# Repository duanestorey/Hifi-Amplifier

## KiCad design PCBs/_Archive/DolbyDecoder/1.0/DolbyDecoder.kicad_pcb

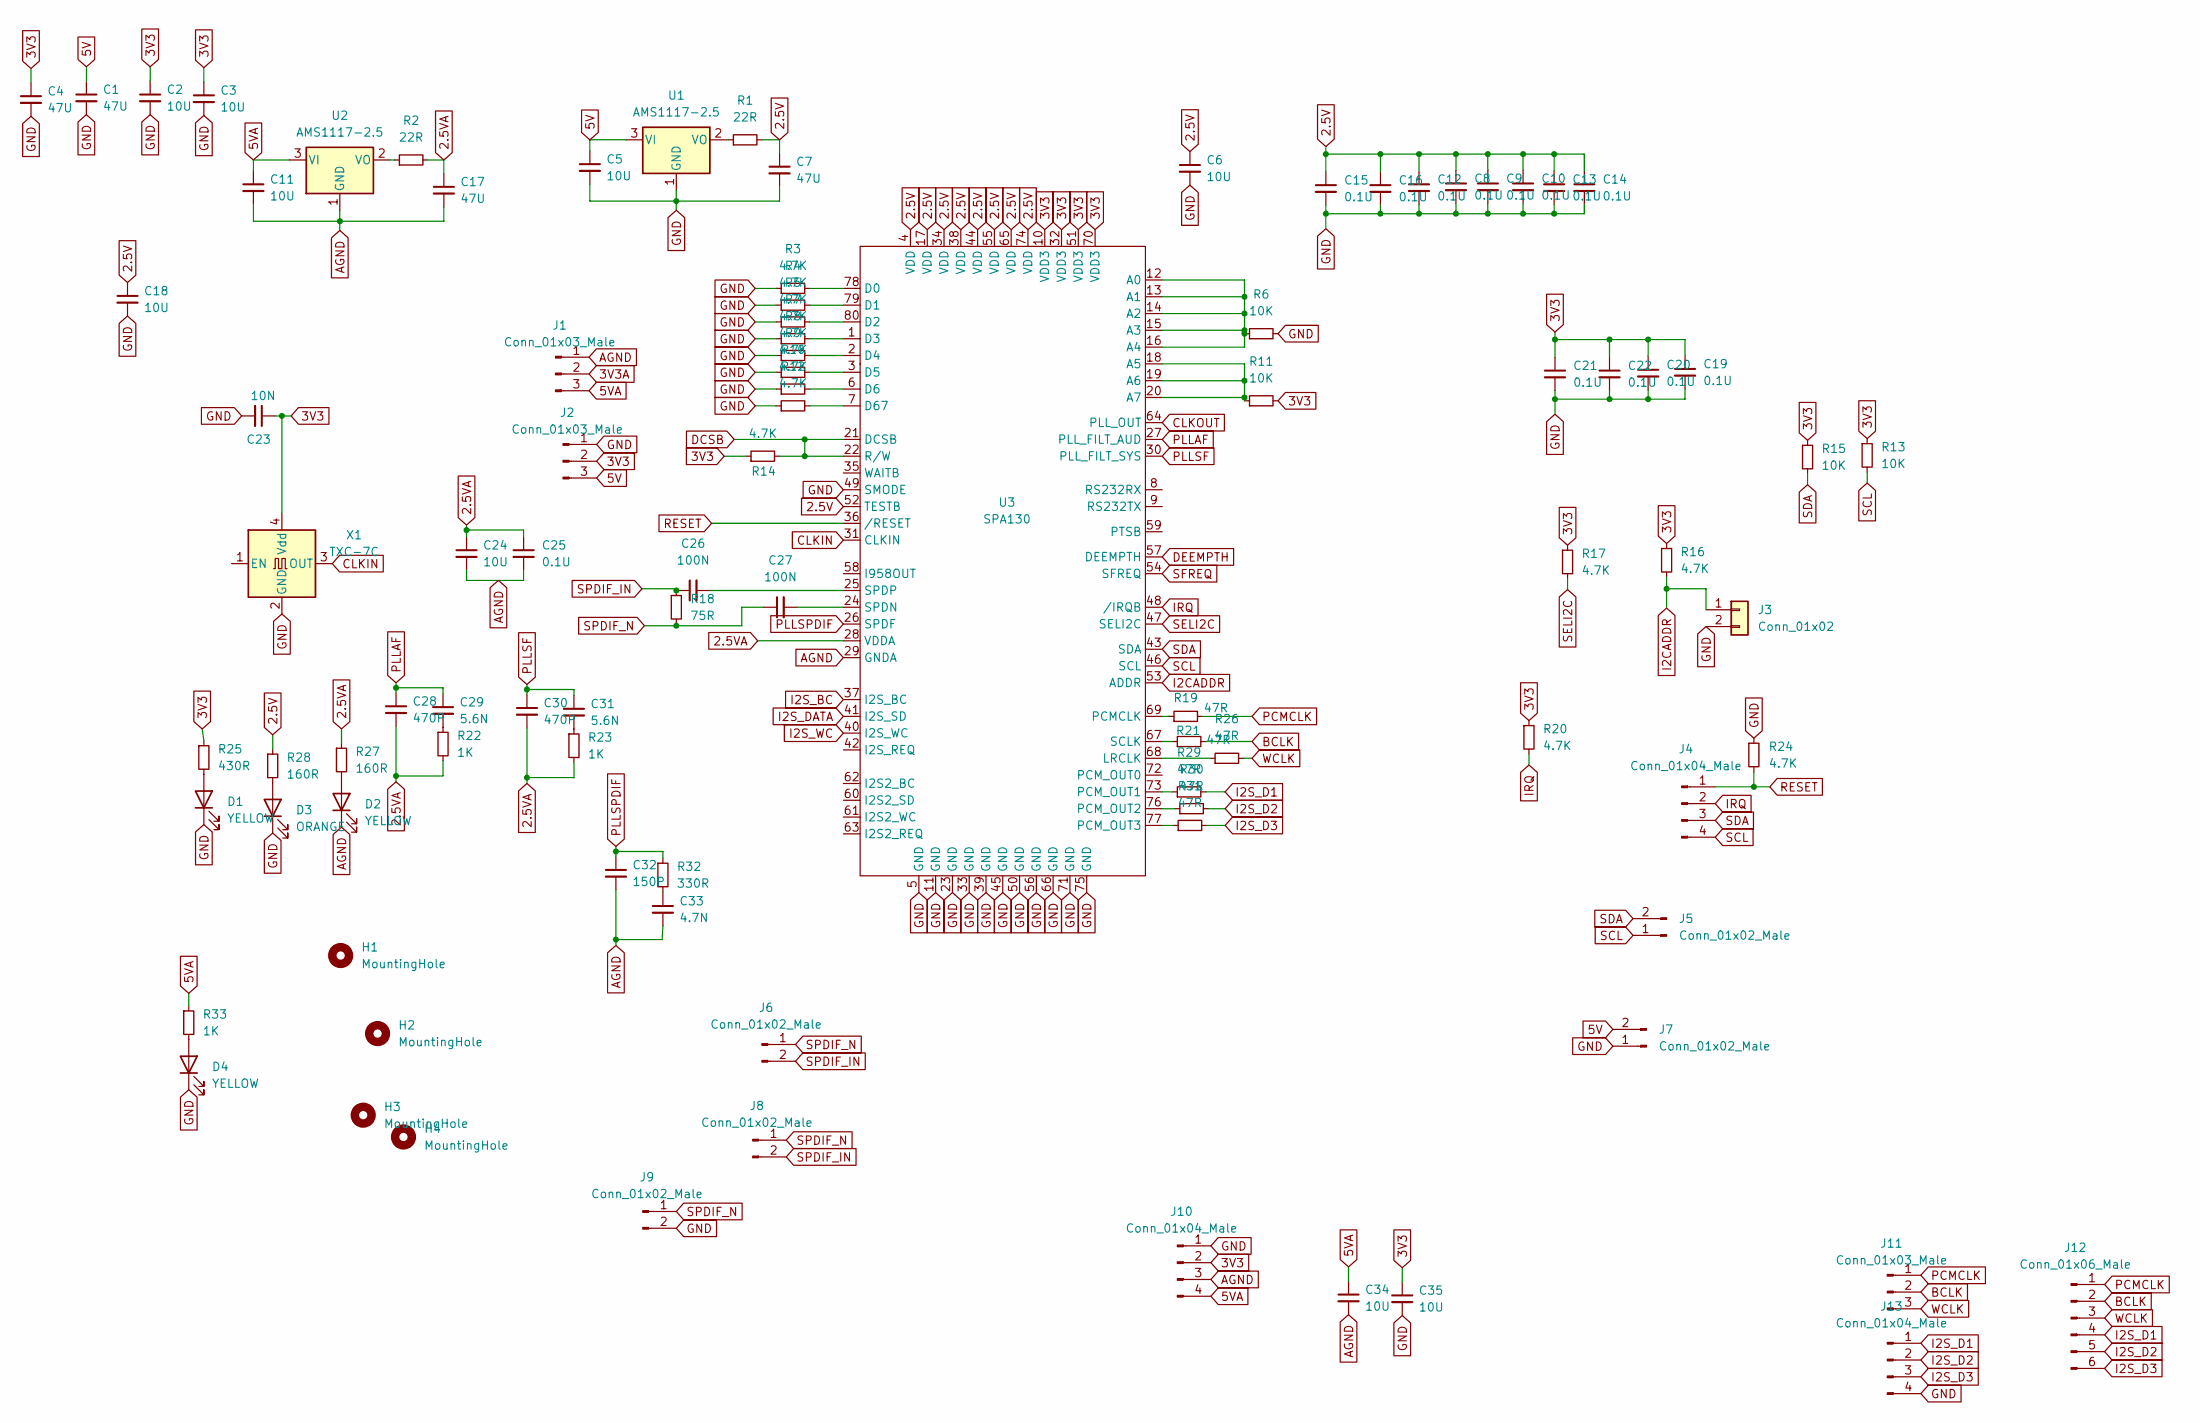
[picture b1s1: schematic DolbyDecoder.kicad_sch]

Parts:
C1, C4, C7, C17: 47U; C_1206_3216Metric_Pad1.33x1.80mm_HandSolder
C2, C3, C6, C18, C34, C35: 10U; C_1206_3216Metric_Pad1.33x1.80mm_HandSolder
C5, C11, C24: 10U; C_0805_2012Metric_Pad1.18x1.45mm_HandSolder
C8, C9, C10, C12, C13, C14, C15, C16, C19, C20, C21, C22, C25: 0.1U; C_0603_1608Metric_Pad1.08x0.95mm_HandSolder
C23: 10N; C_0603_1608Metric_Pad1.08x0.95mm_HandSolder
C26, C27: 100N; C_0805_2012Metric_Pad1.18x1.45mm_HandSolder
C28, C30: 470P; C_0805_2012Metric_Pad1.18x1.45mm_HandSolder
C29, C31: 5.6N; C_0805_2012Metric_Pad1.18x1.45mm_HandSolder
C32: 150P; C_0805_2012Metric_Pad1.18x1.45mm_HandSolder
C33: 4.7N; C_0805_2012Metric_Pad1.18x1.45mm_HandSolder
D1, D2, D4: YELLOW; LED_0805_2012Metric_Pad1.15x1.40mm_HandSolder
D3: ORANGE; LED_0805_2012Metric_Pad1.15x1.40mm_HandSolder
H1, H2, H3, H4: MountingHole; MountingHole_3.2mm_M3
J1, J2, J11: Conn_01x03_Male; JST_PH_B3B-PH-K_1x03_P2.00mm_Vertical
J3: Conn_01x02; PinHeader_1x02_P2.54mm_Vertical
J4, J10, J13: Conn_01x04_Male; JST_PH_B4B-PH-K_1x04_P2.00mm_Vertical
J5, J6, J7: Conn_01x02_Male; JST_PH_B2B-PH-K_1x02_P2.00mm_Vertical
J8, J9: Conn_01x02_Male; PinHeader_1x02_P2.54mm_Vertical
J12: Conn_01x06_Male; PinHeader_1x06_P2.54mm_Vertical
R1, R2: 22R; R_0805_2012Metric_Pad1.20x1.40mm_HandSolder
R3, R4, R5, R7, R8, R9, R10, R12, R14, R16, R17, R20, R24: 4.7K; R_0603_1608Metric_Pad0.98x0.95mm_HandSolder
R6, R11, R13, R15: 10K; R_0603_1608Metric_Pad0.98x0.95mm_HandSolder
R18: 75R; R_0603_1608Metric_Pad0.98x0.95mm_HandSolder
R19, R21, R26, R29, R30, R31: 47R; R_0805_2012Metric_Pad1.20x1.40mm_HandSolder
R22, R23, R33: 1K; R_0603_1608Metric_Pad0.98x0.95mm_HandSolder
R25: 430R; R_0603_1608Metric_Pad0.98x0.95mm_HandSolder
R27, R28: 160R; R_0603_1608Metric_Pad0.98x0.95mm_HandSolder
R32: 330R; R_0603_1608Metric_Pad0.98x0.95mm_HandSolder
U1, U2: AMS1117-2.5; SOT-223
U3: SPA130; LQFP-80_14x14mm_P0.65mm
X1: TXC-7C; Oscillator_SMD_EuroQuartz_XO32-4Pin_3.2x2.5mm_HandSoldering

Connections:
2.5V: C6.1, C7.1, C8.1, C9.1, C10.1, C12.1, C13.1, C14.1, C15.1, C16.1, C18.1, R1.2, R28.1, U3.4 (VDD), U3.17 (VDD), U3.34 (VDD), U3.38 (VDD), U3.44 (VDD), U3.52 (TESTB), U3.55 (VDD), U3.65 (VDD), U3.74 (VDD)
2.5VA: C17.1, C24.1, C25.1, C28.2, C30.2, R2.2, R22.2, R23.2, R27.1, U3.28 (VDDA)
3V3: C2.1, C3.1, C4.1, C19.1, C20.1, C21.1, C22.1, C23.1, C35.1, J2.2, J10.2, R11.2, R13.1, R14.1, R15.1, R16.1, R17.1, R20.1, R25.1, U3.10 (VDD3), U3.32 (VDD3), U3.51 (VDD3), U3.70 (VDD3), X1.4 (Vdd)
3V3A: J1.2
5V: C1.1, C5.1, J2.3, J7.2, U1.3 (VI)
5VA: C11.1, C34.1, J1.3, J10.4, R33.1, U2.3 (VI)
AGND: C11.2, C17.2, C24.2, C25.2, C32.2, C33.2, C34.2, D2.1 (K), J1.1, J10.3, U2.1 (GND), U3.29 (GNDA)
BCLK: J11.2, J12.2, R21.2
CLKIN: U3.31 (CLKIN), X1.3 (OUT)
CLKOUT: U3.64 (PLL_OUT)
DCSB: R14.2, U3.21 (DCSB), U3.22 (R/W)
DEEMPTH: U3.57 (DEEMPTH)
GND: C1.2, C2.2, C3.2, C4.2, C5.2, C6.2, C7.2, C8.2, C9.2, C10.2, C12.2, C13.2, C14.2, C15.2, C16.2, C18.2, C19.2, C20.2, C21.2, C22.2, C23.2, C35.2, D1.1 (K), D3.1 (K), D4.1 (K), J2.1, J3.2, J7.1, J9.2, J10.1, J13.4, R3.1, R4.1, R5.1, R6.2, R7.1, R8.1, R9.1, R10.1, R12.1, R24.1, U1.1 (GND), U3.5 (GND), U3.11 (GND), U3.23 (GND), U3.33 (GND), U3.39 (GND), U3.45 (GND), U3.49 (SMODE), U3.50 (GND), U3.56 (GND), U3.66 (GND), U3.71 (GND), U3.75 (GND), X1.2 (GND)
I2CADDR: J3.1, R16.2, U3.53 (ADDR)
I2S_BC: U3.37 (I2S_BC)
I2S_D1: J12.4, J13.1, R29.2
I2S_D2: J12.5, J13.2, R30.2
I2S_D3: J12.6, J13.3, R31.2
I2S_DATA: U3.41 (I2S_SD)
I2S_WC: U3.40 (I2S_WC)
IRQ: J4.2, R20.2, U3.48 (/IRQB)
unnamed: C29.2, R22.1
unnamed: C31.2, R23.1
unnamed: C33.1, R32.2
unnamed: D1.2 (A), R25.2
unnamed: D2.2 (A), R27.2
unnamed: D3.2 (A), R28.2
unnamed: D4.2 (A), R33.2
unnamed: R1.1, U1.2 (VO)
unnamed: R2.1, U2.2 (VO)
unnamed: R6.1, U3.12 (A0), U3.13 (A1), U3.14 (A2), U3.15 (A3), U3.16 (A4)
unnamed: R11.1, U3.18 (A5), U3.19 (A6), U3.20 (A7)
unnamed: R3.2, U3.78 (D0)
unnamed: R4.2, U3.79 (D1)
unnamed: R5.2, U3.80 (D2)
unnamed: R7.2, U3.1 (D3)
unnamed: R8.2, U3.2 (D4)
unnamed: R9.2, U3.3 (D5)
unnamed: R10.2, U3.6 (D6)
unnamed: R12.2, U3.7 (D67)
unnamed: R26.1, U3.68 (LRCLK)
unnamed: R19.1, U3.69 (PCMCLK)
unnamed: R29.1, U3.73 (PCM_OUT1)
unnamed: R30.1, U3.76 (PCM_OUT2)
unnamed: R31.1, U3.77 (PCM_OUT3)
unnamed: R21.1, U3.67 (SCLK)
unnamed: C27.2, U3.24 (SPDN)
unnamed: C26.2, U3.25 (SPDP)
PCMCLK: J11.1, J12.1, R19.2
PLLAF: C28.1, C29.1, U3.27 (PLL_FILT_AUD)
PLLSF: C30.1, C31.1, U3.30 (PLL_FILT_SYS)
PLLSPDIF: C32.1, R32.1, U3.26 (SPDF)
RESET: J4.1, R24.2, U3.36 (/RESET)
SCL: J4.4, J5.1, R13.2, U3.46 (SCL)
SDA: J4.3, J5.2, R15.2, U3.43 (SDA)
SELI2C: R17.2, U3.47 (SELI2C)
SFREQ: U3.54 (SFREQ)
SPDIF_IN: C26.1, J6.2, J8.2, R18.1
SPDIF_N: C27.1, J6.1, J8.1, J9.1, R18.2
WCLK: J11.3, J12.3, R26.2

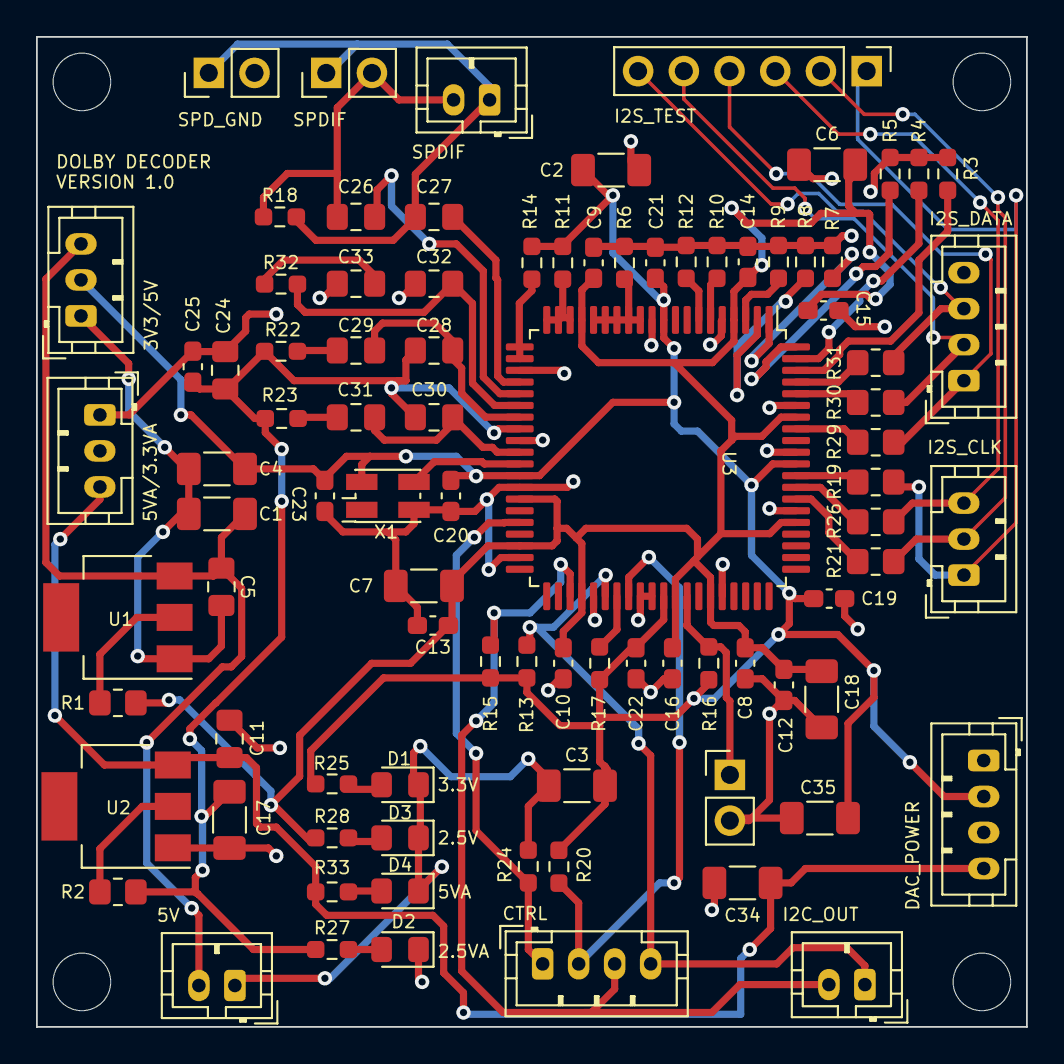
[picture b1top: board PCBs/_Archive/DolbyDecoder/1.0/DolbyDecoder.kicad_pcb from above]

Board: 2 copper layers, 55.0 x 55.0 mm, 93 parts (0 on the bottom side), 53 nets.

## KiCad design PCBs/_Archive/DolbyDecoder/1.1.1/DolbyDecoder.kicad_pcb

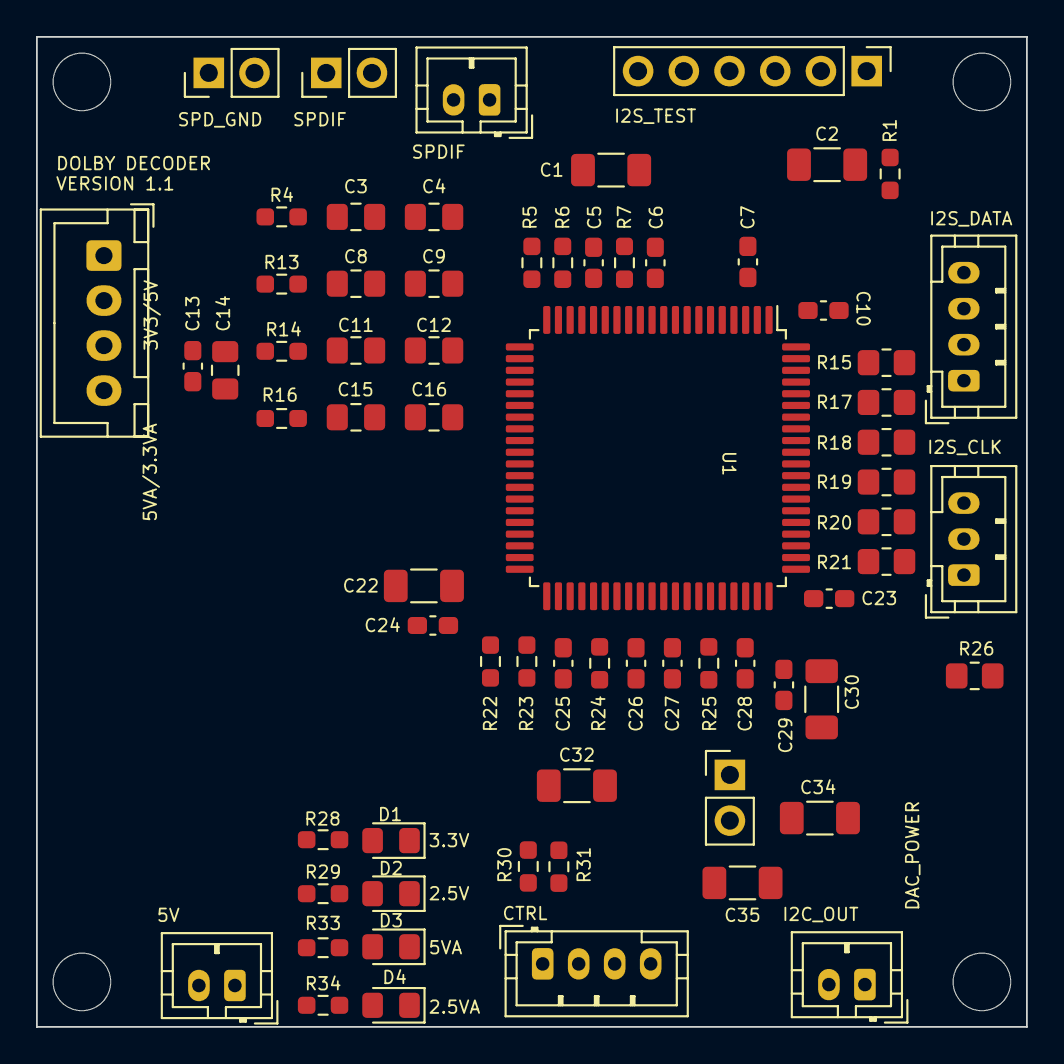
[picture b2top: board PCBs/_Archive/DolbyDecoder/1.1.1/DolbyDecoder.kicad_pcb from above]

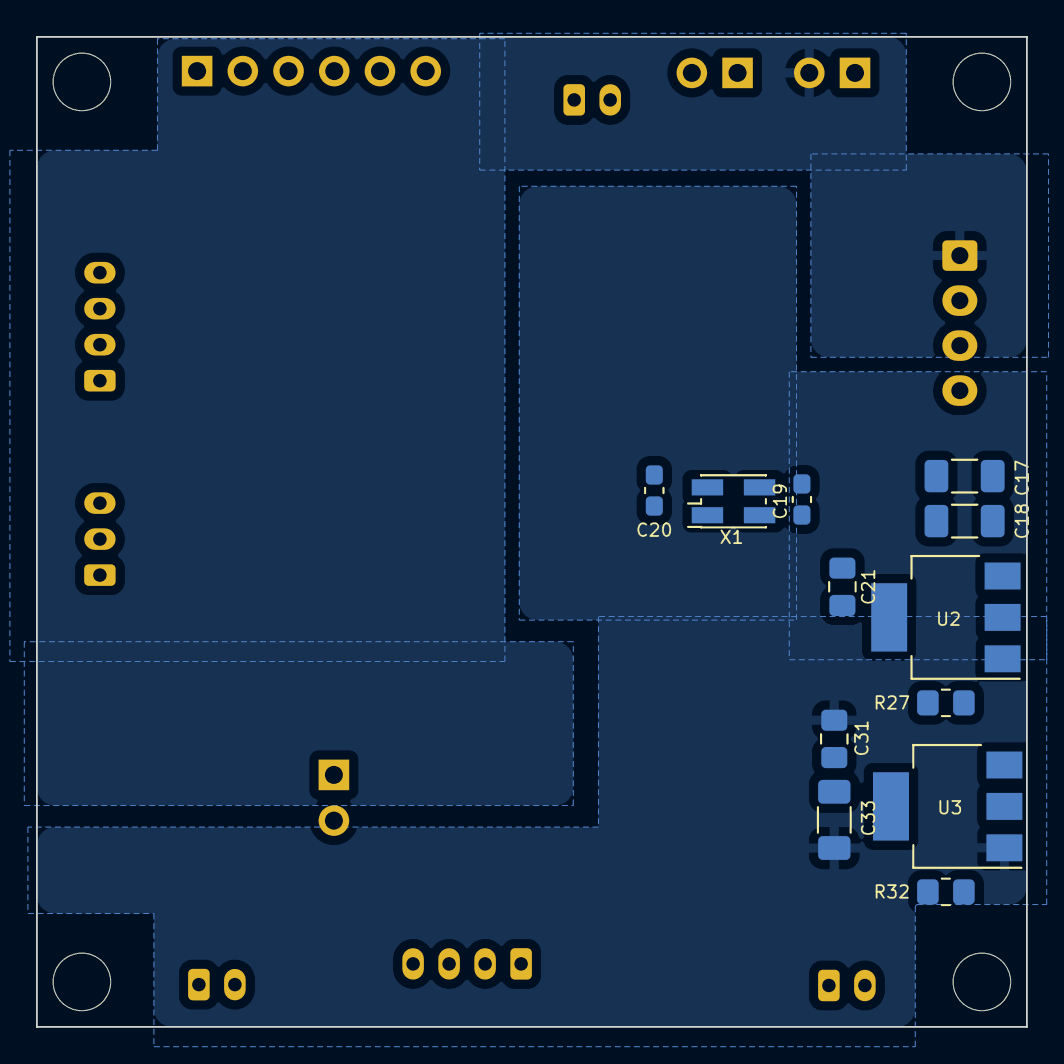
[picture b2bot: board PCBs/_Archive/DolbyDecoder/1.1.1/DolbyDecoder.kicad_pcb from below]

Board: 2 copper layers, 55.0 x 55.0 mm, 85 parts (12 on the bottom side), 48 nets, no tracks yet.

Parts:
C1, C2, C17, C18, C22, C30, C32, C33, C34, C35: 10U; C_1206_3216Metric_Pad1.33x1.80mm_HandSolder
C3, C4: 100N; C_0805_2012Metric_Pad1.18x1.45mm_HandSolder
C5, C6, C7, C10, C13, C20, C23, C24, C25, C26, C27, C28, C29: 0.1U; C_0603_1608Metric_Pad1.08x0.95mm_HandSolder
C8: 4.7N; C_0805_2012Metric_Pad1.18x1.45mm_HandSolder
C9: 150P; C_0805_2012Metric_Pad1.18x1.45mm_HandSolder
C11, C15: 5.6N; C_0805_2012Metric_Pad1.18x1.45mm_HandSolder
C12, C16: 470P; C_0805_2012Metric_Pad1.18x1.45mm_HandSolder
C14, C21, C31: 10U; C_0805_2012Metric_Pad1.18x1.45mm_HandSolder
C19: 100N; C_0603_1608Metric_Pad1.08x0.95mm_HandSolder
D1, D3, D4: YELLOW; LED_0805_2012Metric_Pad1.15x1.40mm_HandSolder
D2: ORANGE; LED_0805_2012Metric_Pad1.15x1.40mm_HandSolder
H1, H2, H3, H4: MountingHole; MountingHole_3.2mm_M3
J1, J2: Conn_01x02_Male; PinHeader_1x02_P2.54mm_Vertical
J3: Conn_01x06_Male; PinHeader_1x06_P2.54mm_Vertical
J4, J12, J13: Conn_01x02_Male; JST_PH_B2B-PH-K_1x02_P2.00mm_Vertical
J6, J11: Conn_01x04_Male; JST_PH_B4B-PH-K_1x04_P2.00mm_Vertical
J8: Conn_01x03_Male; JST_PH_B3B-PH-K_1x03_P2.00mm_Vertical
J9: Conn_01x04_Male; JST_XH_B4B-XH-A_1x04_P2.50mm_Vertical
J10: Conn_01x02; PinHeader_1x02_P2.54mm_Vertical
R1, R5, R24, R25, R30, R31: 4.7K; R_0603_1608Metric_Pad0.98x0.95mm_HandSolder
R4: 75R; R_0603_1608Metric_Pad0.98x0.95mm_HandSolder
R6, R7, R22, R23: 10K; R_0603_1608Metric_Pad0.98x0.95mm_HandSolder
R13: 330R; R_0603_1608Metric_Pad0.98x0.95mm_HandSolder
R14, R16, R33: 1K; R_0603_1608Metric_Pad0.98x0.95mm_HandSolder
R15, R17, R18, R19, R20, R21, R26: 47R; R_0805_2012Metric_Pad1.20x1.40mm_HandSolder
R27, R32: 22R; R_0805_2012Metric_Pad1.20x1.40mm_HandSolder
R28: 430R; R_0603_1608Metric_Pad0.98x0.95mm_HandSolder
R29, R34: 160R; R_0603_1608Metric_Pad0.98x0.95mm_HandSolder
U1: SPA130; LQFP-80_14x14mm_P0.65mm
U2, U3: AMS1117-2.5; SOT-223
X1: TXC-7C; Oscillator_SMD_EuroQuartz_XO32-4Pin_3.2x2.5mm_HandSoldering

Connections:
2.5V: C2.1, C5.1, C7.1, C10.1, C22.1, C24.1, C25.1, C27.1, C28.1, C29.1, C30.1, R27.2, R29.1, U1.4 (VDD), U1.17 (VDD), U1.34 (VDD), U1.38 (VDD), U1.44 (VDD), U1.52 (TESTB), U1.55 (VDD), U1.65 (VDD), U1.74 (VDD)
2.5VA: C12.2, C13.1, C14.1, C16.2, C33.1, R14.2, R16.2, R32.2, R34.1, U1.28 (VDDA)
3V3: C1.1, C6.1, C17.1, C19.1, C20.1, C23.1, C26.1, C32.1, C34.1, J9.2, R5.1, R6.2, R22.1, R23.1, R24.1, R25.1, R28.1, R31.1, U1.10 (VDD3), U1.32 (VDD3), U1.51 (VDD3), U1.70 (VDD3), X1.4 (Vdd)
5V: C18.1, C21.1, J9.4, J12.2, U2.3 (VI)
5VA: C31.1, C35.1, R33.1, U3.3 (VI)
AGND: C8.2, C9.2, C13.2, C14.2, C31.2, C33.2, C35.2, D4.1 (K), J9.3, U1.29 (GNDA), U3.1 (GND)
BCLK: J3.2, J8.2, R21.2
CLKIN: U1.31 (CLKIN), X1.3 (OUT)
GND: C1.2, C2.2, C5.2, C6.2, C7.2, C10.2, C17.2, C18.2, C19.2, C20.2, C21.2, C22.2, C23.2, C24.2, C25.2, C26.2, C27.2, C28.2, C29.2, C30.2, C32.2, C34.2, D1.1 (K), D2.1 (K), D3.1 (K), J1.2, J9.1, J10.2, J12.1, R7.2, R30.1, U1.5 (GND), U1.11 (GND), U1.23 (GND), U1.33 (GND), U1.39 (GND), U1.45 (GND), U1.49 (SMODE), U1.50 (GND), U1.56 (GND), U1.66 (GND), U1.71 (GND), U1.75 (GND), U2.1 (GND), X1.2 (GND)
I2CADDR: J10.1, R25.2, U1.53 (ADDR)
I2S_D1: J3.4, J6.1, R18.2
I2S_D2: J3.5, J6.2, R17.2
I2S_D3: J3.6, J6.3, R15.2
I2S_D4: J6.4, R26.2
IRQ: J11.2, R31.2, U1.48 (/IRQB)
unnamed: C8.1, R13.2
unnamed: C11.2, R14.1
unnamed: C15.2, R16.1
unnamed: D1.2 (A), R28.2
unnamed: D2.2 (A), R29.2
unnamed: D3.2 (A), R33.2
unnamed: D4.2 (A), R34.2
unnamed: R7.1, U1.12 (A0), U1.13 (A1), U1.14 (A2), U1.15 (A3), U1.16 (A4)
unnamed: R6.1, U1.18 (A5), U1.19 (A6), U1.20 (A7)
unnamed: R1.2, U1.21 (DCSB)
unnamed: R20.1, U1.68 (LRCLK)
unnamed: R19.1, U1.69 (PCMCLK)
unnamed: R26.1, U1.72 (PCM_OUT0)
unnamed: R18.1, U1.73 (PCM_OUT1)
unnamed: R17.1, U1.76 (PCM_OUT2)
unnamed: R15.1, U1.77 (PCM_OUT3)
unnamed: R5.2, U1.22 (R/W)
unnamed: R21.1, U1.67 (SCLK)
unnamed: C4.2, U1.24 (SPDN)
unnamed: C3.2, U1.25 (SPDP)
unnamed: R27.1, U2.2 (VO)
unnamed: R32.1, U3.2 (VO)
PCMCLK: J3.1, J8.1, R19.2
PLLAF: C11.1, C12.1, U1.27 (PLL_FILT_AUD)
PLLSF: C15.1, C16.1, U1.30 (PLL_FILT_SYS)
PLLSPDIF: C9.1, R13.1, U1.26 (SPDF)
RESET: J11.1, R30.2, U1.36 (/RESET)
SCL: J11.4, J13.1, R23.2, U1.46 (SCL)
SDA: J11.3, J13.2, R22.2, U1.43 (SDA)
SELI2C: R24.2, U1.47 (SELI2C)
SPDIF_IN: C3.1, J2.2, J4.2, R4.1
SPDIF_N: C4.1, J1.1, J2.1, J4.1, R4.2
WCLK: J3.3, J8.3, R20.2

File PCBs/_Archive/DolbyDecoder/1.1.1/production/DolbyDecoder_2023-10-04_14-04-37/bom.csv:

Designator,Footprint,Quantity,Value,LCSC Part #
"C1, C17, C18, C2, C22, C30, C32, C33, C34, C35",1206,10,10U,
"C10, C13, C20, C23, C24, C25, C26, C27, C28, C29, C5, C6, C7",0603,13,0.1U,
"C11, C15",0805,2,5.6N,
"C12, C16",0805,2,470P,
"C14, C21, C31",0805,3,10U,
C19,0603,1,10N,
"C3, C4",0805,2,100N,
C8,0805,1,4.7N,
C9,0805,1,150P,
"D1, D3, D4",0805,3,YELLOW,
D2,0805,1,ORANGE,
"H1, H2, H3, H4",MountingHole_3.2mm_M3,4,MountingHole,
"J1, J2",PinHeader_1x02_P2.54mm_Vertical,2,Conn_01x02_Male,
J10,PinHeader_1x02_P2.54mm_Vertical,1,Conn_01x02,
"J11, J6, J9",JST_PH_B4B-PH-K_1x04_P2.00mm_Vertical,3,Conn_01x04_Male,
"J12, J13, J4",JST_PH_B2B-PH-K_1x02_P2.00mm_Vertical,3,Conn_01x02_Male,
J3,PinHeader_1x06_P2.54mm_Vertical,1,Conn_01x06_Male,
"J5, J7, J8",JST_PH_B3B-PH-K_1x03_P2.00mm_Vertical,3,Conn_01x03_Male,
"R1, R10, R11, R12, R2, R24, R25, R3, R30, R31, R5, R8, R9",0603,13,4.7K,
R13,0603,1,330R,
"R14, R16, R33",0603,3,1K,
"R15, R17, R18, R19, R20, R21, R26",0805,7,47R,
"R22, R23, R6, R7",0603,4,10K,
"R27, R32",0805,2,22R,
R28,0603,1,430R,
"R29, R34",0603,2,160R,
R4,0603,1,75R,
U1,LQFP-80_14x14mm_P0.65mm,1,SPA130,
"U2, U3",SOT-223,2,AMS1117-2.5,
X1,Oscillator_SMD_EuroQuartz_XO32-4Pin_3.2x2.5mm_HandSoldering,1,TXC-7C,

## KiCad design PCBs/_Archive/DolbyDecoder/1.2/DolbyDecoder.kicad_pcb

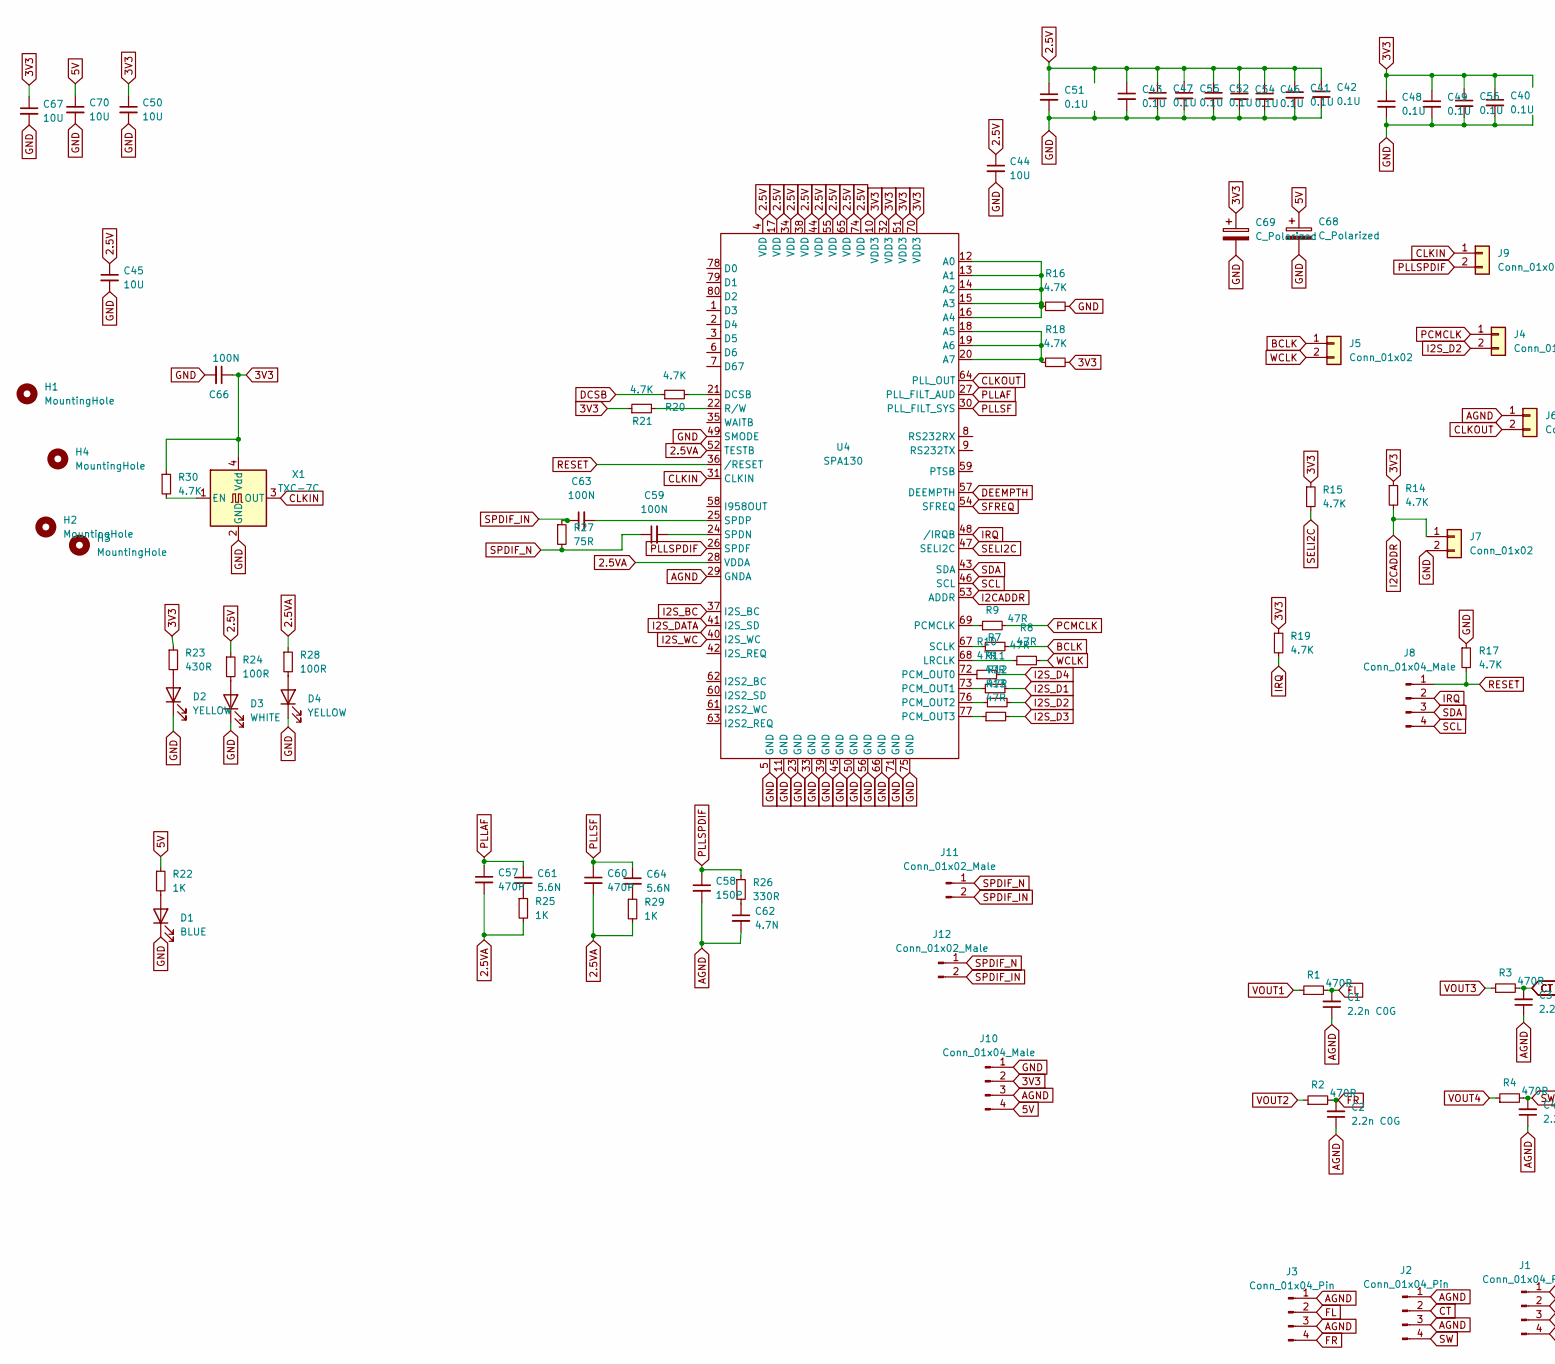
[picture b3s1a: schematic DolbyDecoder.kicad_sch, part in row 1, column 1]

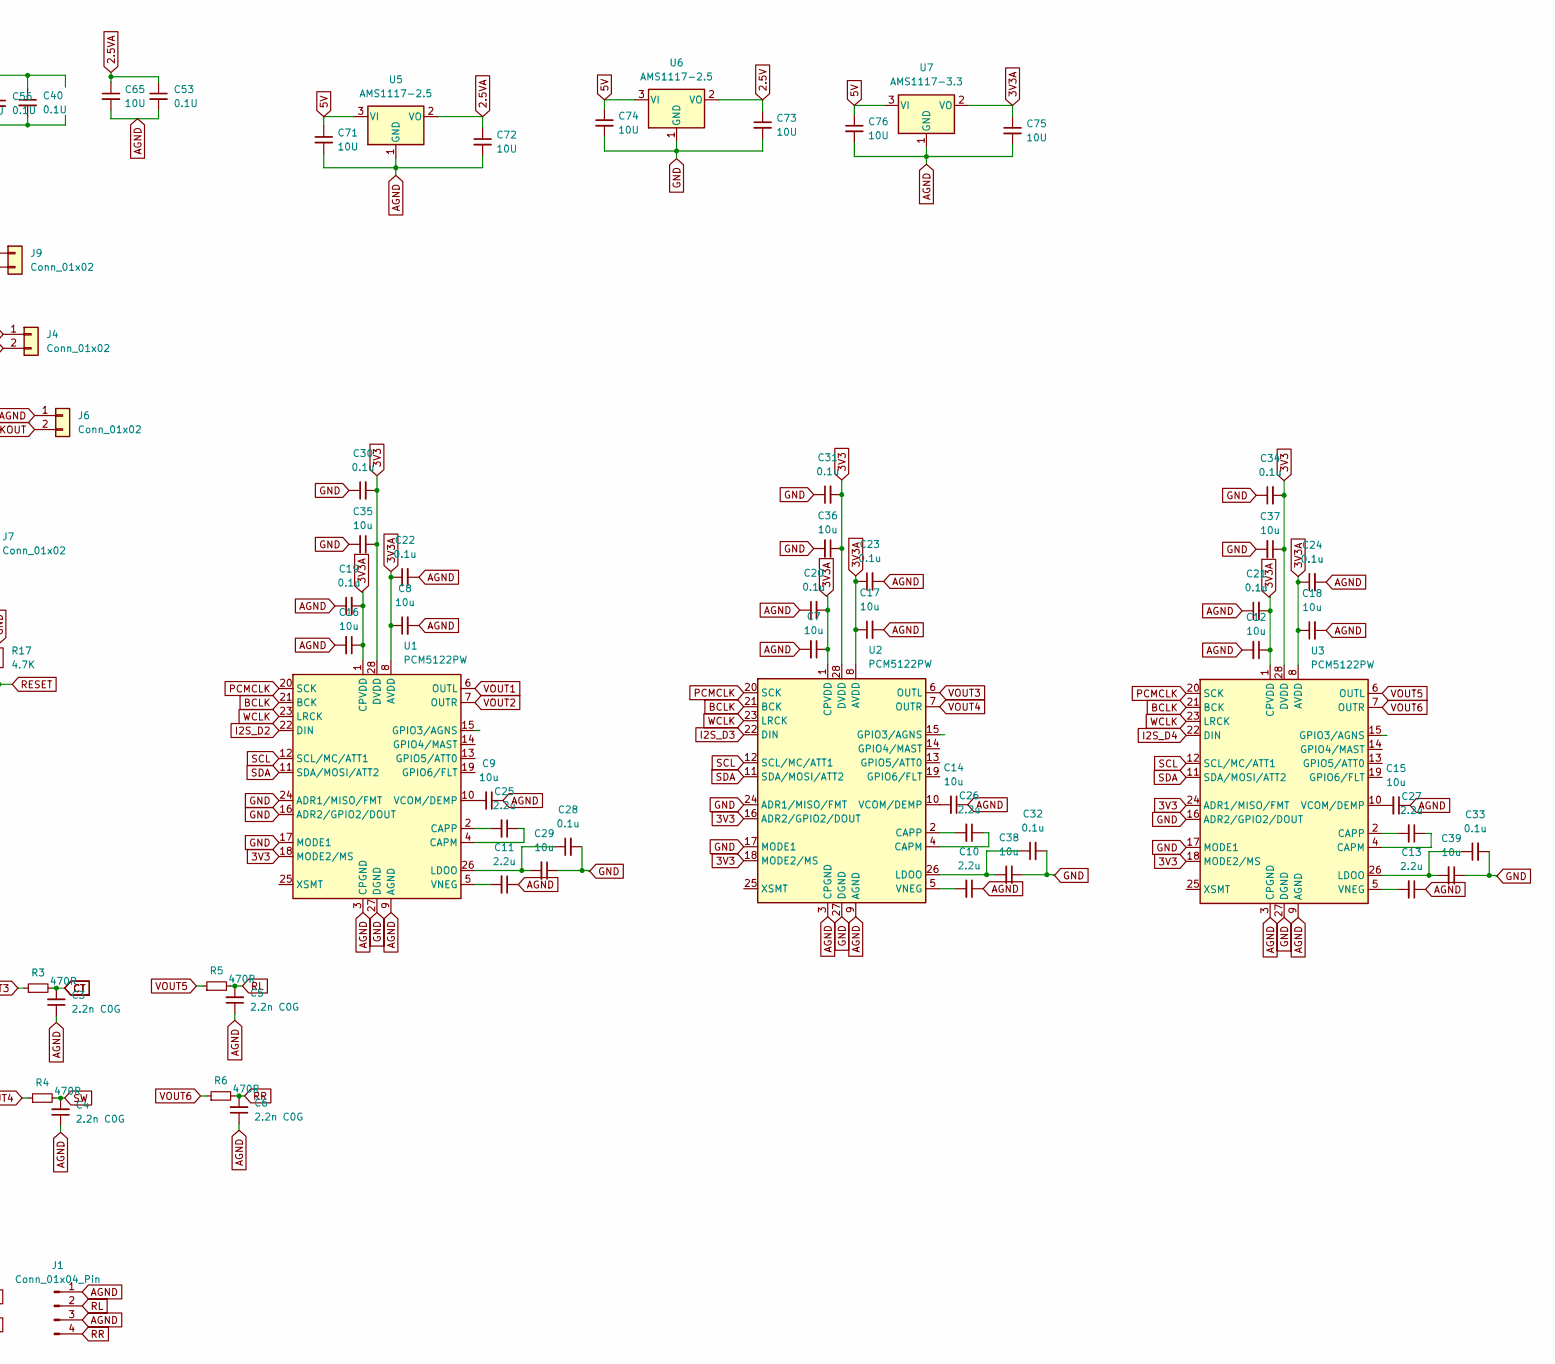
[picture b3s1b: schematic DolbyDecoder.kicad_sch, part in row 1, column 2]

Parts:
C1, C2, C3, C4, C5, C6: 2.2n C0G; C_1206_3216Metric_Pad1.33x1.80mm_HandSolder
C7, C8, C9, C12, C14, C15, C16, C17, C18, C29, C35, C36, C37, C38, C39: 10u; C_1206_3216Metric_Pad1.33x1.80mm_HandSolder
C10, C11, C13, C25, C26, C27: 2.2u; C_1206_3216Metric_Pad1.33x1.80mm_HandSolder
C19, C20, C21, C22, C23, C24, C28, C30, C31, C32, C33, C34: 0.1u; C_0805_2012Metric_Pad1.18x1.45mm_HandSolder
C40, C41, C42, C43, C46, C47, C48, C49, C51, C52, C53, C54, C55, C56: 0.1U; C_0603_1608Metric_Pad1.08x0.95mm_HandSolder
C44, C45, C50, C67, C70, C71, C72, C73, C74, C75, C76: 10U; C_1206_3216Metric_Pad1.33x1.80mm_HandSolder
C57, C60: 470P; C_0805_2012Metric_Pad1.18x1.45mm_HandSolder
C58: 150P; C_0805_2012Metric_Pad1.18x1.45mm_HandSolder
C59, C63: 100N; C_0805_2012Metric_Pad1.18x1.45mm_HandSolder
C61, C64: 5.6N; C_0805_2012Metric_Pad1.18x1.45mm_HandSolder
C62: 4.7N; C_0805_2012Metric_Pad1.18x1.45mm_HandSolder
C65: 10U; C_0805_2012Metric_Pad1.18x1.45mm_HandSolder
C66: 100N; C_0603_1608Metric_Pad1.08x0.95mm_HandSolder
C68, C69: C_Polarized; CP_Radial_D6.3mm_P2.50mm
D1: BLUE; LED_0805_2012Metric_Pad1.15x1.40mm_HandSolder
D2, D4: YELLOW; LED_0805_2012Metric_Pad1.15x1.40mm_HandSolder
D3: WHITE; LED_0805_2012Metric_Pad1.15x1.40mm_HandSolder
H1, H2, H3, H4: MountingHole; MountingHole_3.2mm_M3
J1, J2, J3: Conn_01x04_Pin; JST_PH_B4B-PH-K_1x04_P2.00mm_Vertical
J4, J5, J6, J7, J9: Conn_01x02; PinHeader_1x02_P2.54mm_Vertical
J8, J10: Conn_01x04_Male; JST_PH_B4B-PH-K_1x04_P2.00mm_Vertical
J11: Conn_01x02_Male; JST_PH_B2B-PH-K_1x02_P2.00mm_Vertical
J12: Conn_01x02_Male; PinHeader_1x02_P2.54mm_Vertical
R1, R2, R3, R4, R5, R6: 470R; R_1206_3216Metric_Pad1.30x1.75mm_HandSolder
R7, R8, R9, R10, R11, R12, R13: 47R; R_0805_2012Metric_Pad1.20x1.40mm_HandSolder
R14, R15, R16, R17, R18, R19, R20, R21, R30: 4.7K; R_0603_1608Metric_Pad0.98x0.95mm_HandSolder
R22, R25, R29: 1K; R_0603_1608Metric_Pad0.98x0.95mm_HandSolder
R23: 430R; R_0603_1608Metric_Pad0.98x0.95mm_HandSolder
R24, R28: 100R; R_0603_1608Metric_Pad0.98x0.95mm_HandSolder
R26: 330R; R_0603_1608Metric_Pad0.98x0.95mm_HandSolder
R27: 75R; R_0603_1608Metric_Pad0.98x0.95mm_HandSolder
U1, U2, U3: PCM5122PW; TSSOP-28_4.4x9.7mm_P0.65mm
U4: SPA130; LQFP-80_14x14mm_P0.65mm
U5, U6: AMS1117-2.5; SOT-223
U7: AMS1117-3.3; SOT-223
X1: TXC-7C; Oscillator_SMD_EuroQuartz_XO32-4Pin_3.2x2.5mm_HandSoldering

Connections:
2.5V: C41.1, C42.1, C43.1, C44.1, C45.1, C46.1, C47.1, C51.1, C52.1, C54.1, C55.1, C73.1, R24.1, U4.4 (VDD), U4.17 (VDD), U4.34 (VDD), U4.38 (VDD), U4.44 (VDD), U4.55 (VDD), U4.65 (VDD), U4.74 (VDD), U6.2 (VO)
2.5VA: C53.1, C57.2, C60.2, C65.1, C72.1, R25.2, R28.1, R29.2, U4.28 (VDDA), U4.52 (TESTB), U5.2 (VO)
3V3: C30.2, C31.2, C34.2, C35.1, C36.1, C37.1, C40.1, C48.1, C49.1, C50.1, C56.1, C66.1, C67.1, C69.1, J10.2, R14.1, R15.1, R18.2, R19.1, R21.1, R23.1, R30.1, U1.18 (MODE2/MS), U1.28 (DVDD), U2.16 (ADR2/GPIO2/DOUT), U2.18 (MODE2/MS), U2.28 (DVDD), U3.18 (MODE2/MS), U3.24 (ADR1/MISO/FMT), U3.28 (DVDD), U4.10 (VDD3), U4.32 (VDD3), U4.51 (VDD3), U4.70 (VDD3), X1.4 (Vdd)
3V3A: C7.1, C8.1, C12.1, C16.1, C17.1, C18.1, C19.2, C20.2, C21.2, C22.1, C23.1, C24.1, C75.1, U1.1 (CPVDD), U1.8 (AVDD), U2.1 (CPVDD), U2.8 (AVDD), U3.1 (CPVDD), U3.8 (AVDD), U7.2 (VO)
5V: C68.1, C70.1, C71.1, C74.1, C76.1, J10.4, R22.1, U5.3 (VI), U6.3 (VI), U7.3 (VI)
AGND: C1.1, C2.1, C3.1, C4.1, C5.1, C6.1, C7.2, C8.2, C9.1, C10.1, C11.1, C12.2, C13.1, C14.1, C15.1, C16.2, C17.2, C18.2, C19.1, C20.1, C21.1, C22.2, C23.2, C24.2, C53.2, C58.2, C62.2, C65.2, C71.2, C72.2, C75.2, C76.2, J1.1, J1.3, J2.1, J2.3, J3.1, J3.3, J6.1, J10.3, U1.3 (CPGND), U1.9 (AGND), U2.3 (CPGND), U2.9 (AGND), U3.3 (CPGND), U3.9 (AGND), U4.29 (GNDA), U5.1 (GND), U7.1 (GND)
BCLK: J5.1, R7.2, U1.21 (BCK), U2.21 (BCK), U3.21 (BCK)
CLKIN: J9.1, U4.31 (CLKIN), X1.3 (OUT)
CLKOUT: J6.2, U4.64 (PLL_OUT)
CT: C3.2, J2.2, R3.2
DCSB: R20.1
DEEMPTH: U4.57 (DEEMPTH)
FL: C1.2, J3.2, R1.2
FR: C2.2, J3.4, R2.2
GND: C28.2, C29.1, C30.1, C31.1, C32.2, C33.2, C34.1, C35.2, C36.2, C37.2, C38.1, C39.1, C40.2, C41.2, C42.2, C43.2, C44.2, C45.2, C46.2, C47.2, C48.2, C49.2, C50.2, C51.2, C52.2, C54.2, C55.2, C56.2, C66.2, C67.2, C68.2, C69.2, C70.2, C73.2, C74.2, D1.1 (K), D2.1 (K), D3.1 (K), D4.1 (K), J7.2, J10.1, R16.2, R17.1, U1.16 (ADR2/GPIO2/DOUT), U1.17 (MODE1), U1.24 (ADR1/MISO/FMT), U1.27 (DGND), U2.17 (MODE1), U2.24 (ADR1/MISO/FMT), U2.27 (DGND), U3.16 (ADR2/GPIO2/DOUT), U3.17 (MODE1), U3.27 (DGND), U4.5 (GND), U4.11 (GND), U4.23 (GND), U4.33 (GND), U4.39 (GND), U4.45 (GND), U4.49 (SMODE), U4.50 (GND), U4.56 (GND), U4.66 (GND), U4.71 (GND), U4.75 (GND), U6.1 (GND), X1.2 (GND)
I2CADDR: J7.1, R14.2, U4.53 (ADDR)
I2S_BC: U4.37 (I2S_BC)
I2S_D1: R11.2
I2S_D2: J4.2, R12.2, U1.22 (DIN)
I2S_D3: R13.2, U2.22 (DIN)
I2S_D4: R10.2, U3.22 (DIN)
I2S_DATA: U4.41 (I2S_SD)
I2S_WC: U4.40 (I2S_WC)
IRQ: J8.2, R19.2, U4.48 (/IRQB)
unnamed: C61.2, R25.1
unnamed: C62.1, R26.2
unnamed: C64.2, R29.1
unnamed: D1.2 (A), R22.2
unnamed: D2.2 (A), R23.2
unnamed: D3.2 (A), R24.2
unnamed: D4.2 (A), R28.2
unnamed: C25.1, U1.4 (CAPM)
unnamed: C25.2, U1.2 (CAPP)
unnamed: C28.1, C29.2, U1.26 (LDOO)
unnamed: C9.2, U1.10 (VCOM/DEMP)
unnamed: C11.2, U1.5 (VNEG)
unnamed: C26.1, U2.4 (CAPM)
unnamed: C26.2, U2.2 (CAPP)
unnamed: C32.1, C38.2, U2.26 (LDOO)
unnamed: C14.2, U2.10 (VCOM/DEMP)
unnamed: C10.2, U2.5 (VNEG)
unnamed: C27.1, U3.4 (CAPM)
unnamed: C27.2, U3.2 (CAPP)
unnamed: C33.1, C39.2, U3.26 (LDOO)
unnamed: C15.2, U3.10 (VCOM/DEMP)
unnamed: C13.2, U3.5 (VNEG)
unnamed: R16.1, U4.12 (A0), U4.13 (A1), U4.14 (A2), U4.15 (A3), U4.16 (A4)
unnamed: R18.1, U4.18 (A5), U4.19 (A6), U4.20 (A7)
unnamed: R20.2, U4.21 (DCSB)
unnamed: R8.1, U4.68 (LRCLK)
unnamed: R9.1, U4.69 (PCMCLK)
unnamed: R10.1, U4.72 (PCM_OUT0)
unnamed: R11.1, U4.73 (PCM_OUT1)
unnamed: R12.1, U4.76 (PCM_OUT2)
unnamed: R13.1, U4.77 (PCM_OUT3)
unnamed: R21.2, U4.22 (R/W)
unnamed: R7.1, U4.67 (SCLK)
unnamed: C59.2, U4.24 (SPDN)
unnamed: C63.2, U4.25 (SPDP)
unnamed: R30.2, X1.1 (EN)
PCMCLK: J4.1, R9.2, U1.20 (SCK), U2.20 (SCK), U3.20 (SCK)
PLLAF: C57.1, C61.1, U4.27 (PLL_FILT_AUD)
PLLSF: C60.1, C64.1, U4.30 (PLL_FILT_SYS)
PLLSPDIF: C58.1, J9.2, R26.1, U4.26 (SPDF)
RESET: J8.1, R17.2, U4.36 (/RESET)
RL: C5.2, J1.2, R5.2
RR: C6.2, J1.4, R6.2
SCL: J8.4, U1.12 (SCL/MC/ATT1), U2.12 (SCL/MC/ATT1), U3.12 (SCL/MC/ATT1), U4.46 (SCL)
SDA: J8.3, U1.11 (SDA/MOSI/ATT2), U2.11 (SDA/MOSI/ATT2), U3.11 (SDA/MOSI/ATT2), U4.43 (SDA)
SELI2C: R15.2, U4.47 (SELI2C)
SFREQ: U4.54 (SFREQ)
SPDIF_IN: C63.1, J11.2, J12.2, R27.1
SPDIF_N: C59.1, J11.1, J12.1, R27.2
SW: C4.2, J2.4, R4.2
VOUT1: R1.1, U1.6 (OUTL)
VOUT2: R2.1, U1.7 (OUTR)
VOUT3: R3.1, U2.6 (OUTL)
VOUT4: R4.1, U2.7 (OUTR)
VOUT5: R5.1, U3.6 (OUTL)
VOUT6: R6.1, U3.7 (OUTR)
WCLK: J5.2, R8.2, U1.23 (LRCK), U2.23 (LRCK), U3.23 (LRCK)
